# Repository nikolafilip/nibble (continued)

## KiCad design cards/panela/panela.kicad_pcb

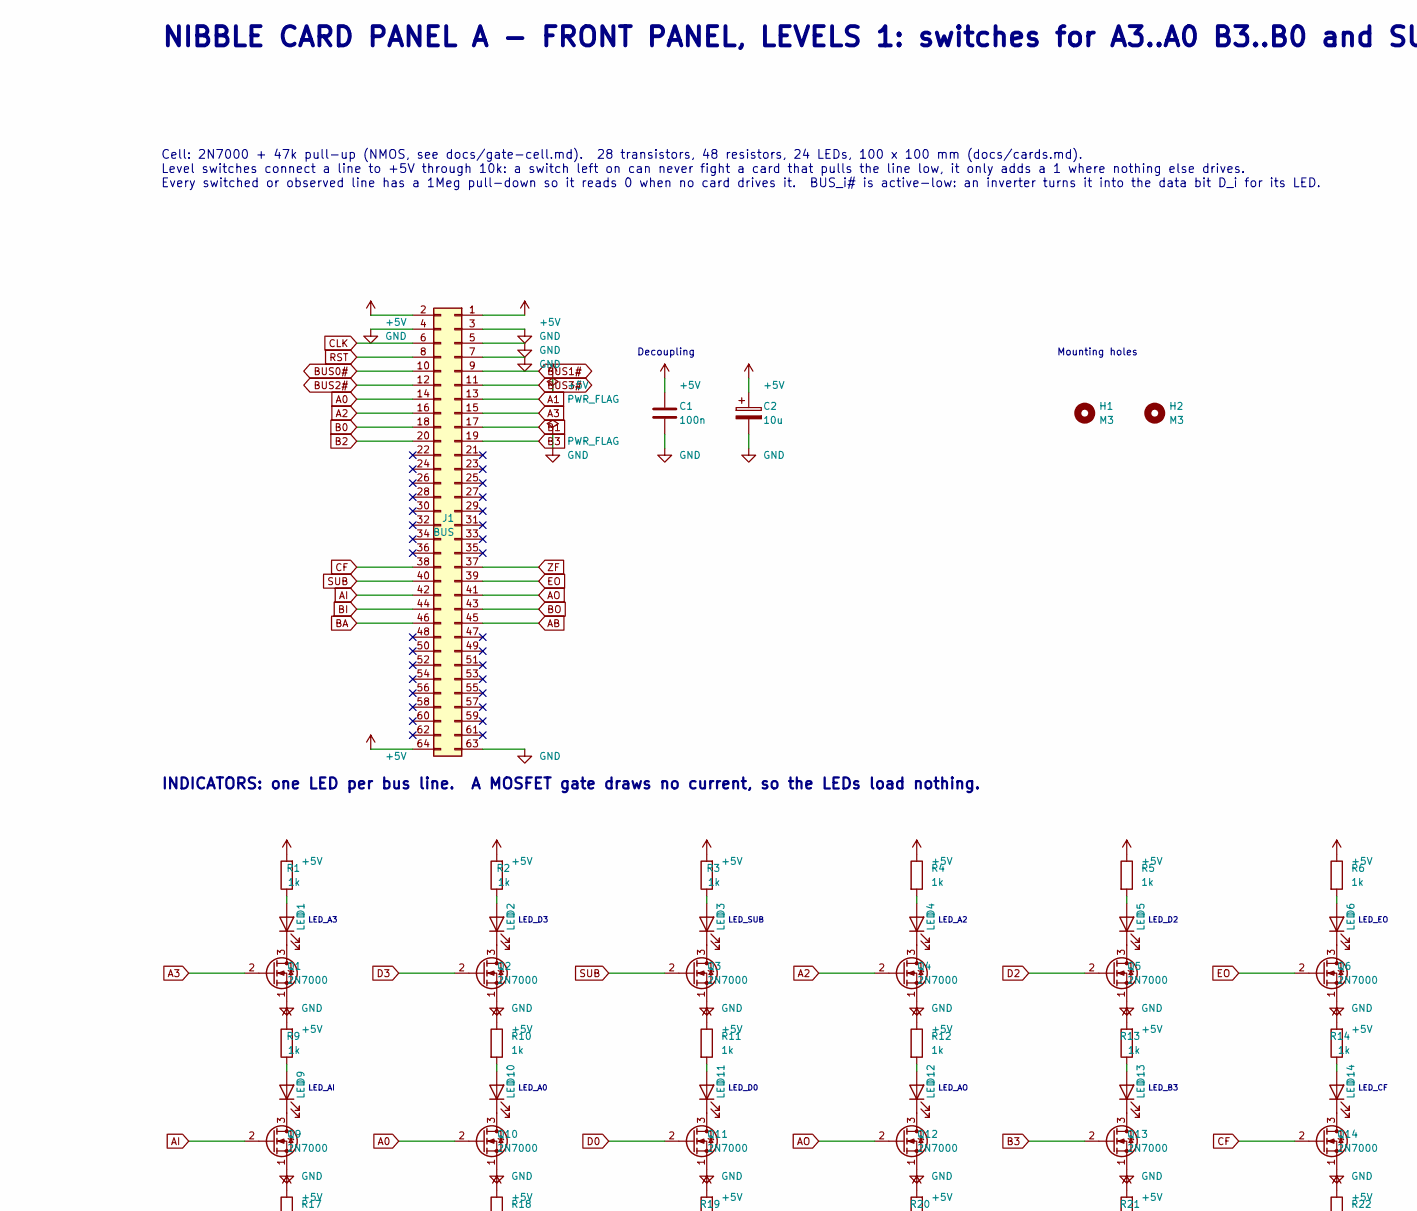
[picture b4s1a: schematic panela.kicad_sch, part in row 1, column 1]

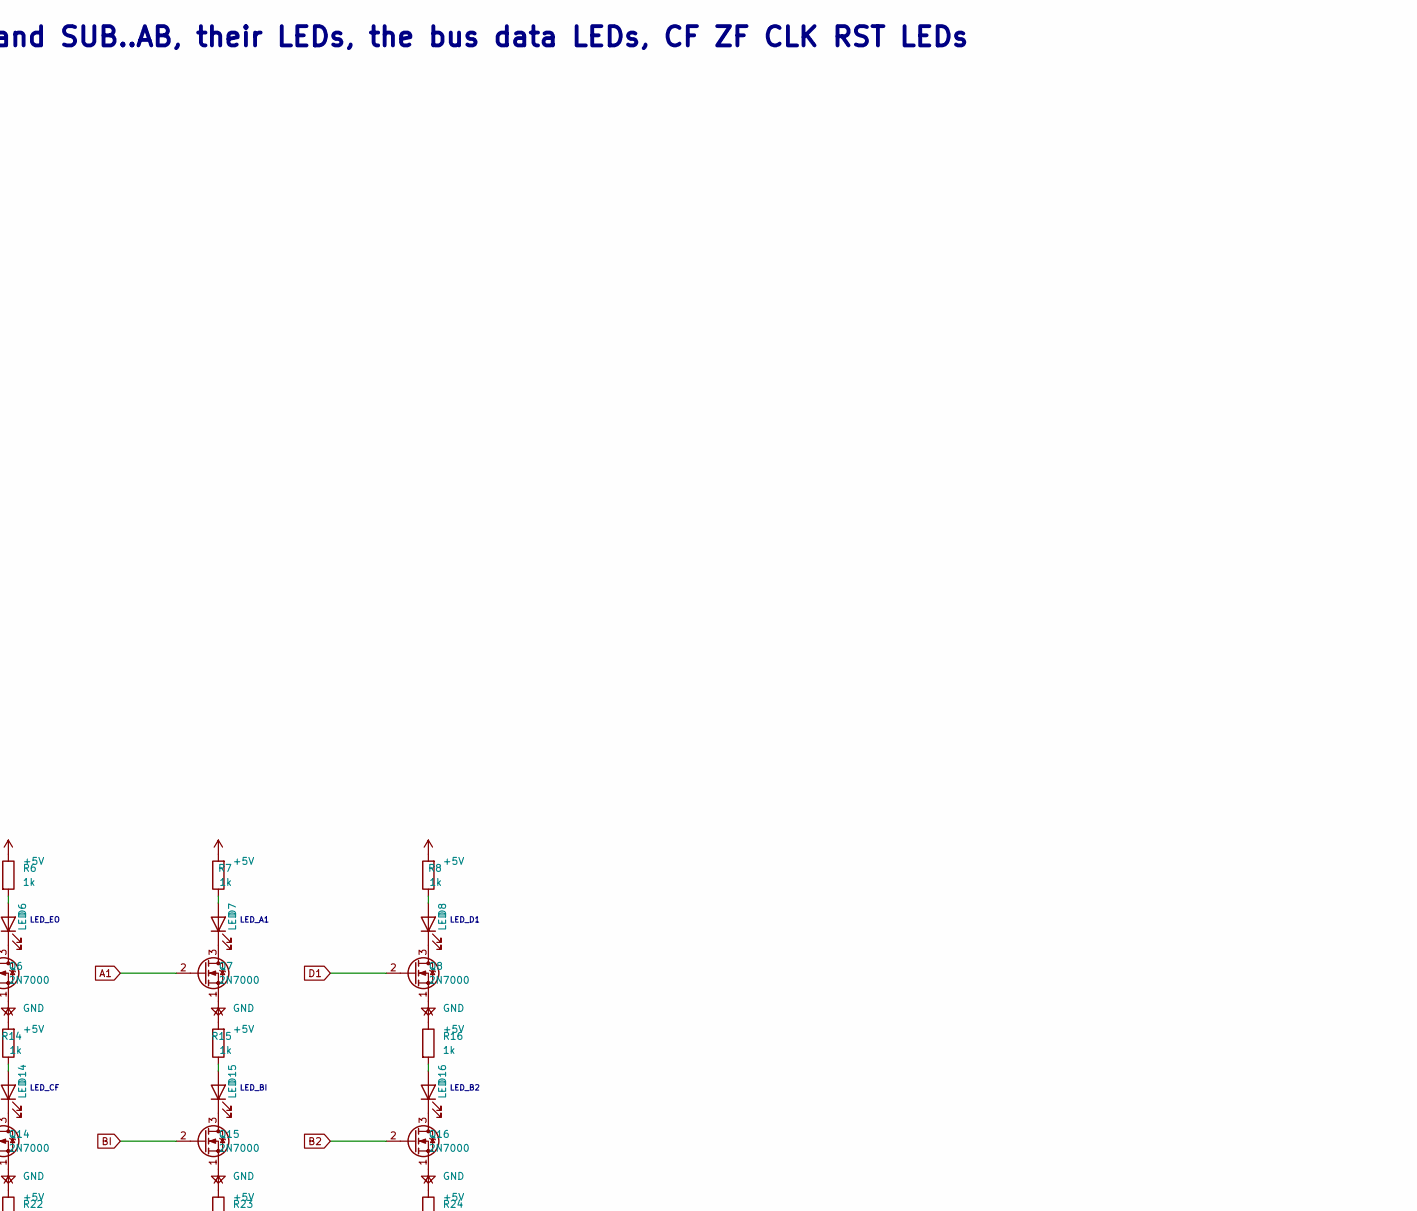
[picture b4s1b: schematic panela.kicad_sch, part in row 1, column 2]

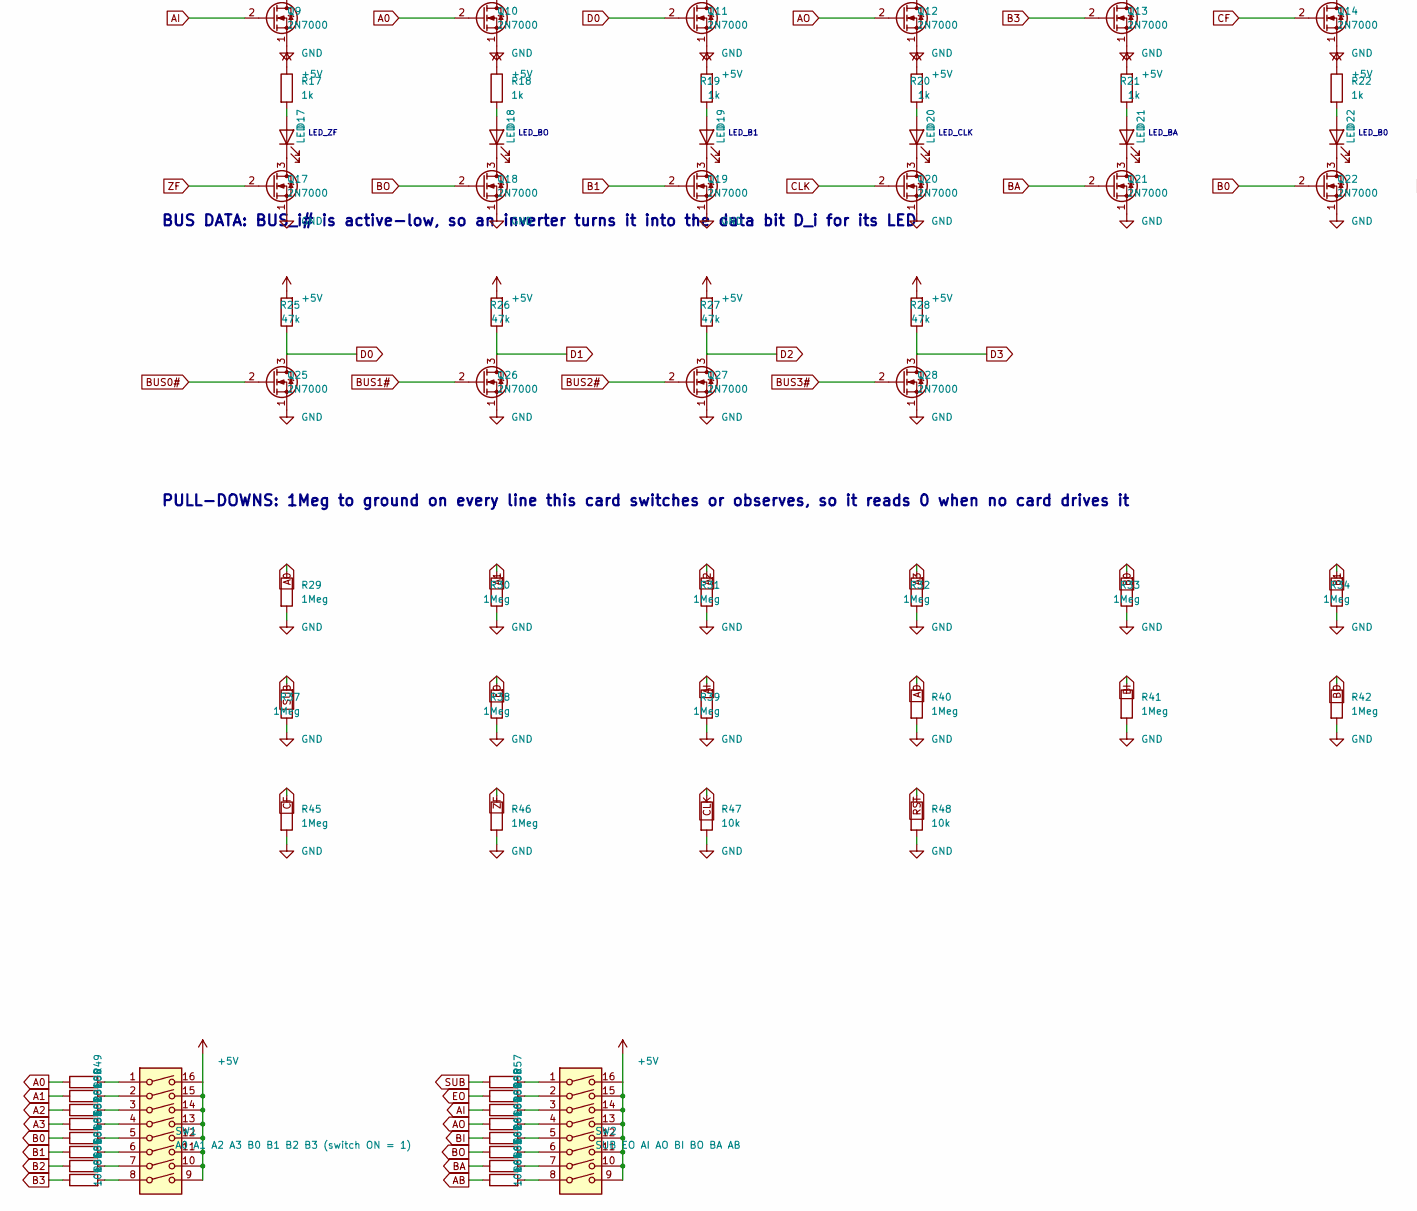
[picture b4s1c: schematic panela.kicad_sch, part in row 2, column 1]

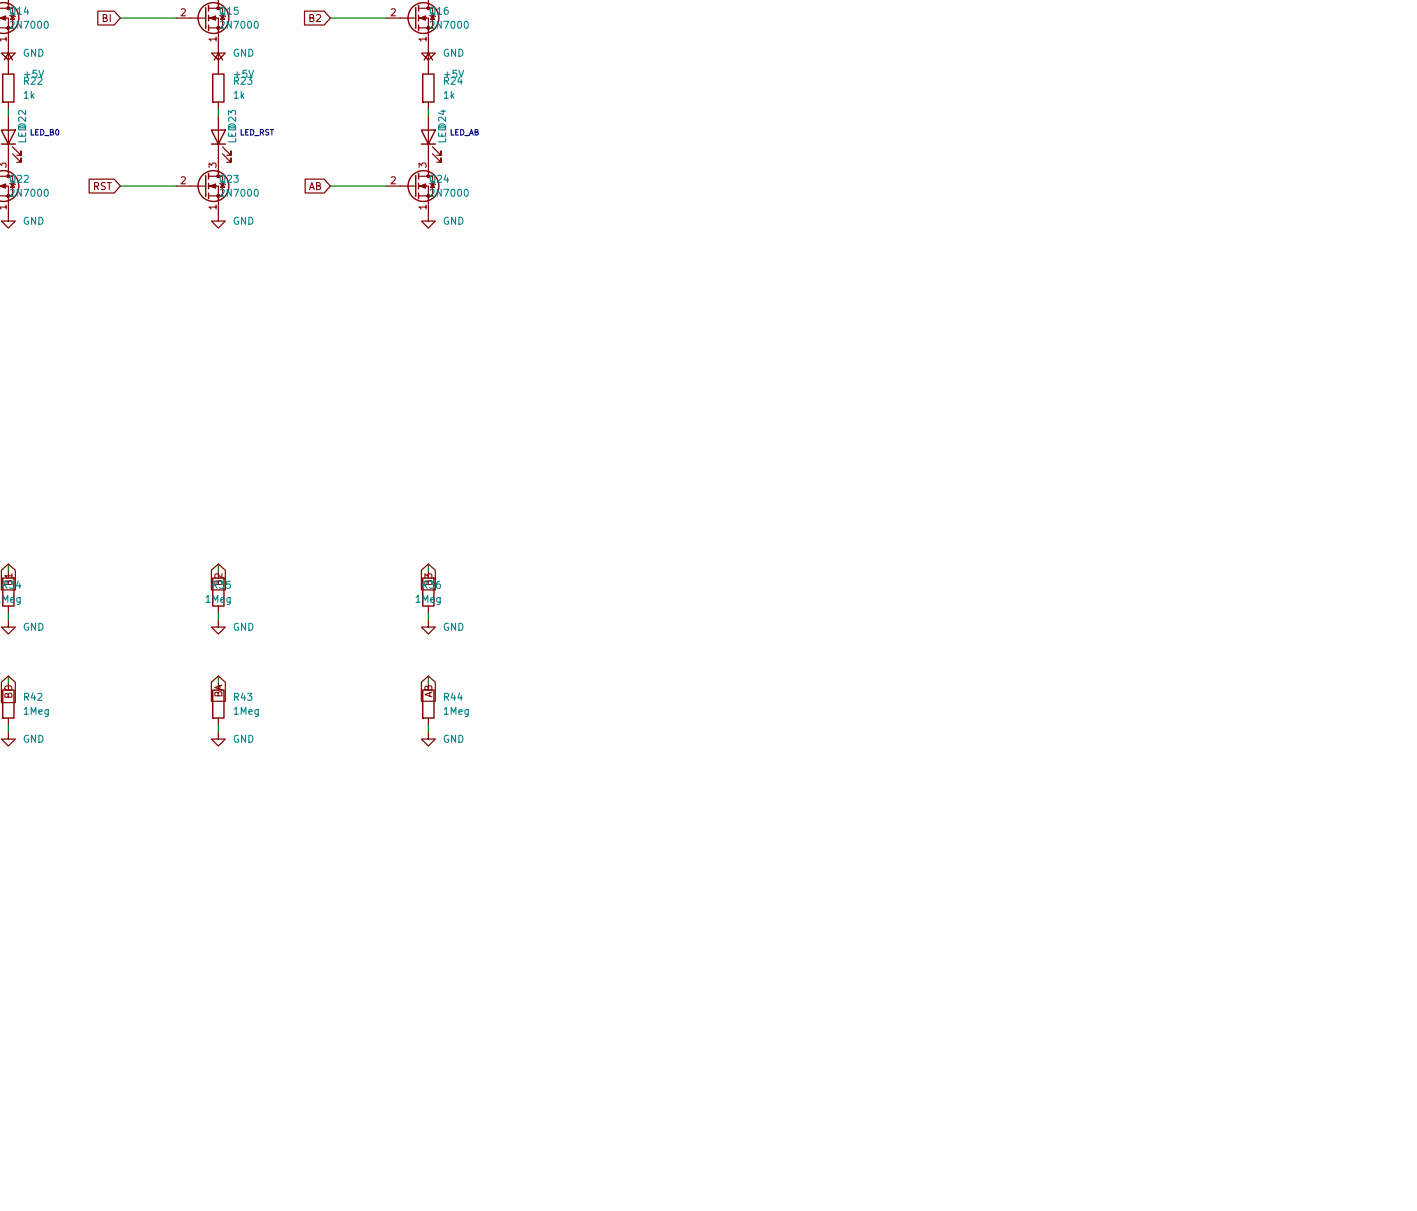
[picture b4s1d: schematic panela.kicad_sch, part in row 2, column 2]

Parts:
C1: 100n; C_Disc_D5.0mm_W2.5mm_P2.50mm
C2: 10u; CP_Radial_D5.0mm_P2.00mm
D1, D2, D3, D4, D5, D6, D7, D8, D9, D10, D11, D12, D13, D14, D15, D16, D17, D18, D19, D20, D21, D22, D23, D24: LED; LED_D3.0mm
H1, H2: M3; MountingHole_3.2mm_M3_Pad
J1: BUS; IDC-Header_2x32_P2.54mm_Vertical
Q1, Q2, Q3, Q4, Q5, Q6, Q7, Q8, Q9, Q10, Q11, Q12, Q13, Q14, Q15, Q16, Q17, Q18, Q19, Q20, Q21, Q22, Q23, Q24, Q25, Q26, Q27, Q28: 2N7000; TO-92_Inline_Wide
R1, R2, R3, R4, R5, R6, R7, R8, R9, R10, R11, R12, R13, R14, R15, R16, R17, R18, R19, R20, R21, R22, R23, R24: 1k; R_Axial_DIN0207_L6.3mm_D2.5mm_P5.08mm_Vertical
R25, R26, R27, R28: 47k; R_Axial_DIN0207_L6.3mm_D2.5mm_P5.08mm_Vertical
R29, R30, R31, R32, R33, R34, R35, R36, R37, R38, R39, R40, R41, R42, R43, R44, R45, R46: 1Meg; R_Axial_DIN0207_L6.3mm_D2.5mm_P5.08mm_Vertical
R47, R48, R49, R50, R51, R52, R53, R54, R55, R56, R57, R58, R59, R60, R61, R62, R63, R64: 10k; R_Axial_DIN0207_L6.3mm_D2.5mm_P5.08mm_Vertical
SW1: A0 A1 A2 A3 B0 B1 B2 B3 (switch ON = 1); SW_DIP_SPSTx08_Slide_9.78x22.5mm_W7.62mm_P2.54mm
SW2: SUB EO AI AO BI BO BA AB; SW_DIP_SPSTx08_Slide_9.78x22.5mm_W7.62mm_P2.54mm

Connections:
+5V: C1.1, C2.1, J1.1, J1.2, J1.64, R1.2, R2.2, R3.2, R4.1, R5.1, R6.1, R7.2, R8.2, R9.2, R10.1, R11.1, R12.1, R13.2, R14.2, R15.2, R16.1, R17.1, R18.1, R19.2, R20.2, R21.2, R22.1, R23.1, R24.1, R25.2, R26.2, R27.2, R28.2, SW1.9, SW1.10, SW1.11, SW1.12, SW1.13, SW1.14, SW1.15, SW1.16, SW2.9, SW2.10, SW2.11, SW2.12, SW2.13, SW2.14, SW2.15, SW2.16
A0: J1.14, Q10.2 (G), R29.1, R49.1
A1: J1.13, Q7.2 (G), R30.2, R50.1
A2: J1.16, Q4.2 (G), R31.2, R51.1
A3: J1.15, Q1.2 (G), R32.2, R52.1
AB: J1.45, Q24.2 (G), R44.1, R64.1
AI: J1.42, Q9.2 (G), R39.2, R59.1
AO: J1.41, Q12.2 (G), R40.1, R60.1
B0: J1.18, Q22.2 (G), R33.2, R53.1
B1: J1.17, Q19.2 (G), R34.2, R54.1
B2: J1.20, Q16.2 (G), R35.2, R55.1
B3: J1.19, Q13.2 (G), R36.2, R56.1
BA: J1.46, Q21.2 (G), R43.1, R63.1
BI: J1.44, Q15.2 (G), R41.1, R61.1
BO: J1.43, Q18.2 (G), R42.1, R62.1
BUS0#: J1.10, Q25.2 (G)
BUS1#: J1.9, Q26.2 (G)
BUS2#: J1.12, Q27.2 (G)
BUS3#: J1.11, Q28.2 (G)
CF: J1.38, Q14.2 (G), R45.1
CLK: J1.6, Q20.2 (G), R47.1
D0: Q11.2 (G), Q25.3 (D), R25.1
D1: Q8.2 (G), Q26.3 (D), R26.1
D2: Q5.2 (G), Q27.3 (D), R27.1
D3: Q2.2 (G), Q28.3 (D), R28.1
EO: J1.39, Q6.2 (G), R38.2, R58.1
GND: C1.2, C2.2, J1.3, J1.4, J1.5, J1.7, J1.63, Q1.1 (S), Q2.1 (S), Q3.1 (S), Q4.1 (S), Q5.1 (S), Q6.1 (S), Q7.1 (S), Q8.1 (S), Q9.1 (S), Q10.1 (S), Q11.1 (S), Q12.1 (S), Q13.1 (S), Q14.1 (S), Q15.1 (S), Q16.1 (S), Q17.1 (S), Q18.1 (S), Q19.1 (S), Q20.1 (S), Q21.1 (S), Q22.1 (S), Q23.1 (S), Q24.1 (S), Q25.1 (S), Q26.1 (S), Q27.1 (S), Q28.1 (S), R29.2, R30.1, R31.1, R32.1, R33.1, R34.1, R35.1, R36.1, R37.1, R38.1, R39.1, R40.2, R41.2, R42.2, R43.2, R44.2, R45.2, R46.2, R47.2, R48.2
unnamed: D1.2 (A), R1.1
unnamed: D1.1 (K), Q1.3 (D)
unnamed: D2.2 (A), R2.1
unnamed: D2.1 (K), Q2.3 (D)
unnamed: D3.2 (A), R3.1
unnamed: D3.1 (K), Q3.3 (D)
unnamed: D4.2 (A), R4.2
unnamed: D4.1 (K), Q4.3 (D)
unnamed: D5.2 (A), R5.2
unnamed: D5.1 (K), Q5.3 (D)
unnamed: D6.2 (A), R6.2
unnamed: D6.1 (K), Q6.3 (D)
unnamed: D7.2 (A), R7.1
unnamed: D7.1 (K), Q7.3 (D)
unnamed: D8.2 (A), R8.1
unnamed: D8.1 (K), Q8.3 (D)
unnamed: D9.2 (A), R9.1
unnamed: D9.1 (K), Q9.3 (D)
unnamed: D10.2 (A), R10.2
unnamed: D10.1 (K), Q10.3 (D)
unnamed: D11.2 (A), R11.2
unnamed: D11.1 (K), Q11.3 (D)
unnamed: D12.2 (A), R12.2
unnamed: D12.1 (K), Q12.3 (D)
unnamed: D13.2 (A), R13.1
unnamed: D13.1 (K), Q13.3 (D)
unnamed: D14.2 (A), R14.1
unnamed: D14.1 (K), Q14.3 (D)
unnamed: D15.2 (A), R15.1
unnamed: D15.1 (K), Q15.3 (D)
unnamed: D16.2 (A), R16.2
unnamed: D16.1 (K), Q16.3 (D)
unnamed: D17.2 (A), R17.2
unnamed: D17.1 (K), Q17.3 (D)
unnamed: D18.2 (A), R18.2
unnamed: D18.1 (K), Q18.3 (D)
unnamed: D19.2 (A), R19.1
unnamed: D19.1 (K), Q19.3 (D)
unnamed: D20.2 (A), R20.1
unnamed: D20.1 (K), Q20.3 (D)
unnamed: D21.2 (A), R21.1
unnamed: D21.1 (K), Q21.3 (D)
unnamed: D22.2 (A), R22.2
unnamed: D22.1 (K), Q22.3 (D)
unnamed: D23.2 (A), R23.2
unnamed: D23.1 (K), Q23.3 (D)
unnamed: D24.2 (A), R24.2
unnamed: D24.1 (K), Q24.3 (D)
unnamed: R49.2, SW1.1
unnamed: R50.2, SW1.2
unnamed: R51.2, SW1.3
unnamed: R52.2, SW1.4
unnamed: R53.2, SW1.5
unnamed: R54.2, SW1.6
unnamed: R55.2, SW1.7
unnamed: R56.2, SW1.8
unnamed: R57.2, SW2.1
unnamed: R58.2, SW2.2
unnamed: R59.2, SW2.3
unnamed: R60.2, SW2.4
unnamed: R61.2, SW2.5
unnamed: R62.2, SW2.6
unnamed: R63.2, SW2.7
unnamed: R64.2, SW2.8
RST: J1.8, Q23.2 (G), R48.1
SUB: J1.40, Q3.2 (G), R37.2, R57.1
ZF: J1.37, Q17.2 (G), R46.1

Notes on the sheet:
NIBBLE CARD PANEL A - FRONT PANEL, LEVELS 1: switches for A3..A0 B3..B0 and SUB..AB, their LEDs, the bus data LEDs, CF ZF CLK RST LEDs
Cell: 2N7000 + 47k pull-up (NMOS, see docs/gate-cell.md). 28 transistors, 48 resistors, 24 LEDs, 100 x 100 mm (docs/cards.md). Level switches connect a line to +5V through 10k: a switch left on can never fight a card that pulls the line low, it only adds a 1 where nothing else drives. Every switche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
INDICATORS: one LED per bus line. A MOSFET gate draws no current, so the LEDs load nothing.
LED_A3
LED_D3
LED_SUB
LED_A2
LED_D2
LED_EO
LED_A1
LED_D1
LED_AI
LED_A0
LED_D0
LED_AO
LED_B3
LED_CF
LED_BI
LED_B2
LED_ZF
LED_BO
LED_B1
LED_CLK
LED_BA
LED_B0
LED_RST
LED_AB
BUS DATA: BUS_i# is active-low, so an inverter turns it into the data bit D_i for its LED
PULL-DOWNS: 1Meg to ground on every line this card switches or observes, so it reads 0 when no card drives it
Decoupling
Mounting holes

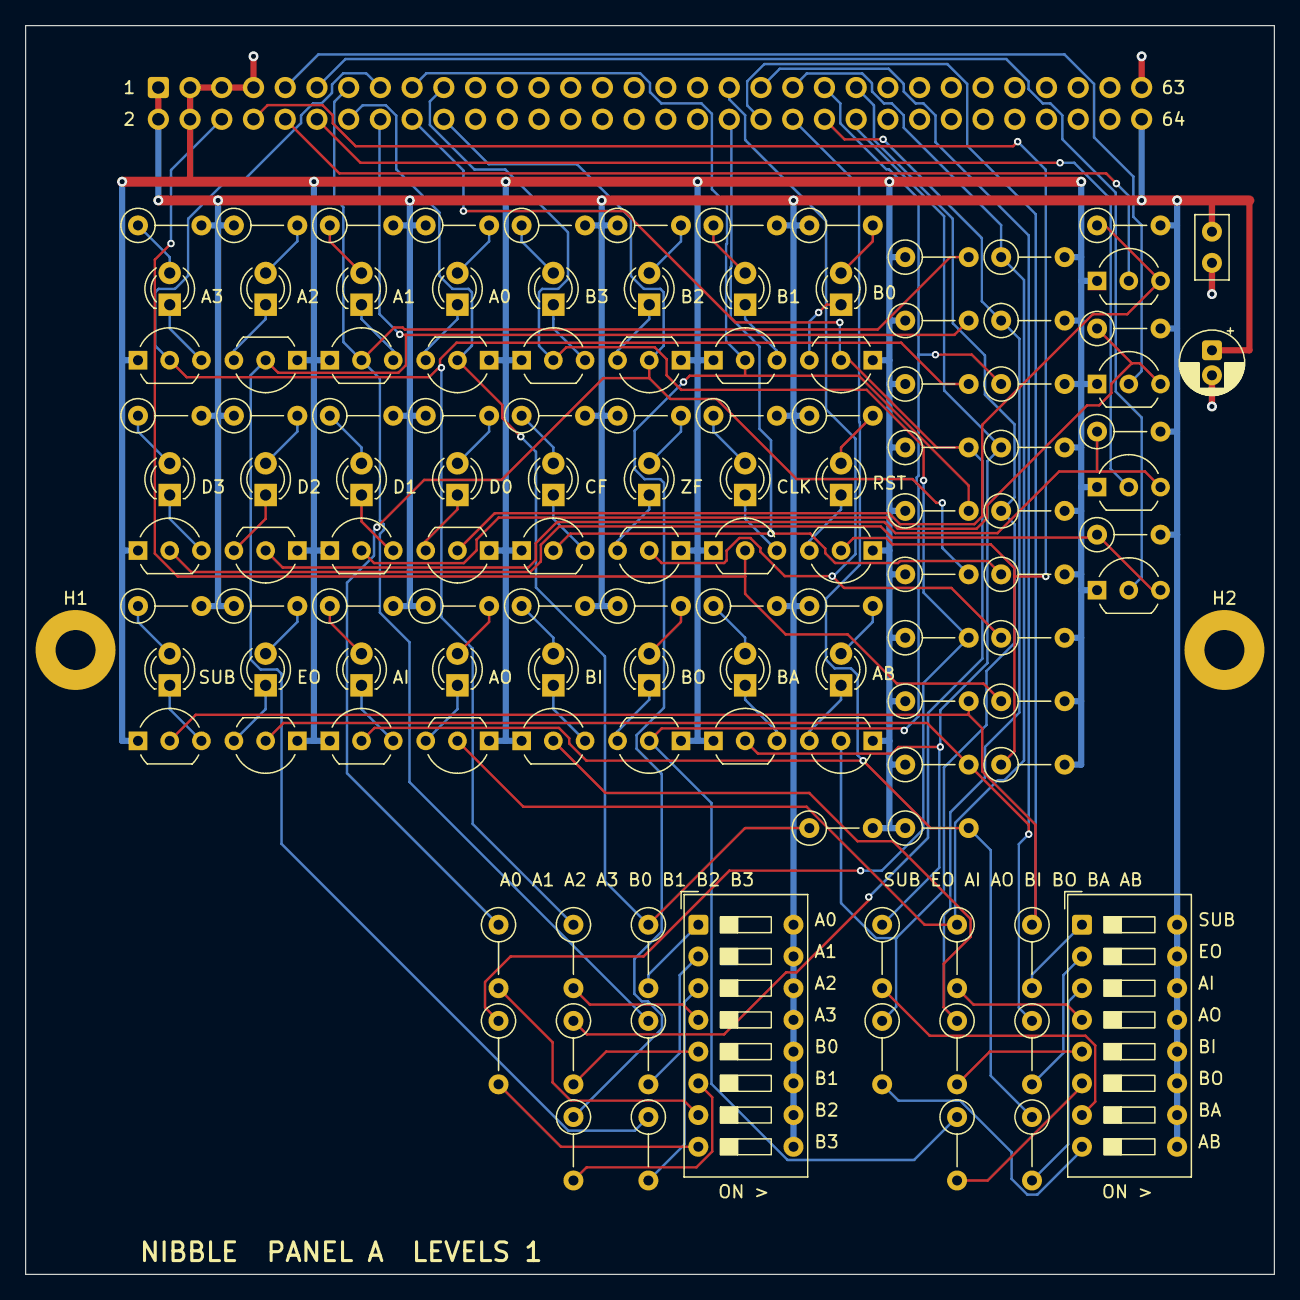
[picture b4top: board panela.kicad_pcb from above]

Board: 2 copper layers, 100.0 x 100.0 mm, 123 parts (1 on the bottom side), 94 nets.

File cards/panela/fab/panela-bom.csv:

"Reference","Value","Footprint","QUANTITY"
"C1","100n","Capacitor_THT:C_Disc_D5.0mm_W2.5mm_P2.50mm","1"
"C2","10u","Capacitor_THT:CP_Radial_D5.0mm_P2.00mm","1"
"D1-D24","LED","LED_THT:LED_D3.0mm","24"
"J1","BUS","Connector_IDC:IDC-Header_2x32_P2.54mm_Vertical","1"
"Q1-Q28","2N7000","Package_TO_SOT_THT:TO-92_Inline_Wide","28"
"R1-R24","1k","Resistor_THT:R_Axial_DIN0207_L6.3mm_D2.5mm_P5.08mm_Vertical","24"
"R25-R28","47k","Resistor_THT:R_Axial_DIN0207_L6.3mm_D2.5mm_P5.08mm_Vertical","4"
"R29-R46","1Meg","Resistor_THT:R_Axial_DIN0207_L6.3mm_D2.5mm_P5.08mm_Vertical","18"
"R47-R64","10k","Resistor_THT:R_Axial_DIN0207_L6.3mm_D2.5mm_P5.08mm_Vertical","18"
"SW1","A0 A1 A2 A3 B0 B1 B2 B3 (switch ON = 1)","Button_Switch_THT:SW_DIP_SPSTx08_Slide_9.78x22.5mm_W7.62mm_P2.54mm","1"
"SW2","SUB EO AI AO BI BO BA AB","Button_Switch_THT:SW_DIP_SPSTx08_Slide_9.78x22.5mm_W7.62mm_P2.54mm","1"

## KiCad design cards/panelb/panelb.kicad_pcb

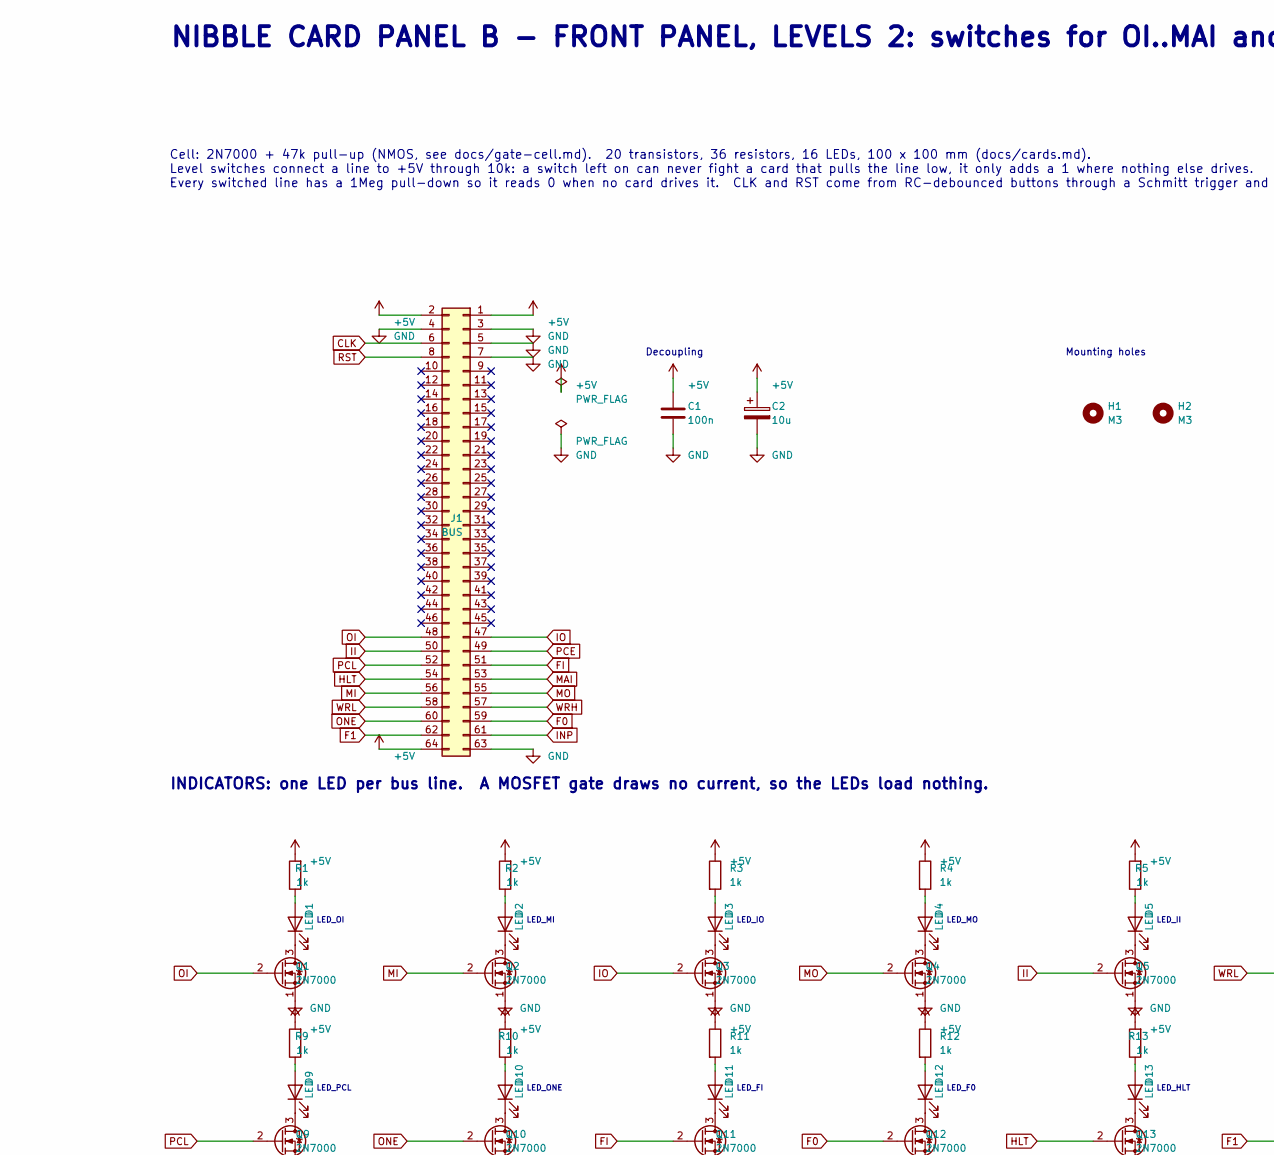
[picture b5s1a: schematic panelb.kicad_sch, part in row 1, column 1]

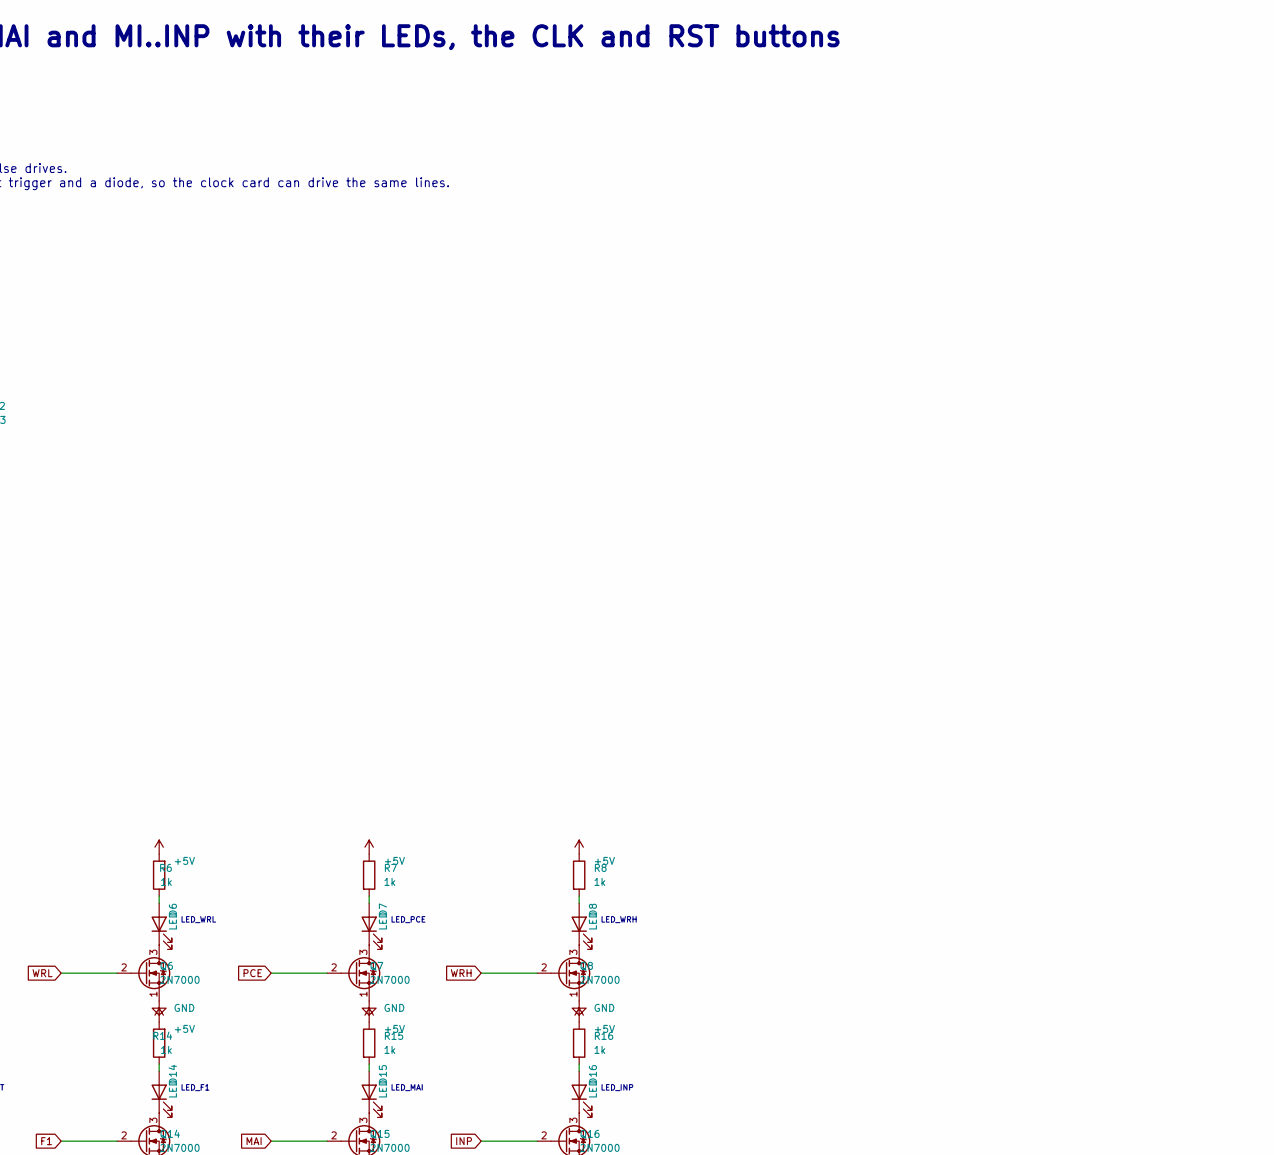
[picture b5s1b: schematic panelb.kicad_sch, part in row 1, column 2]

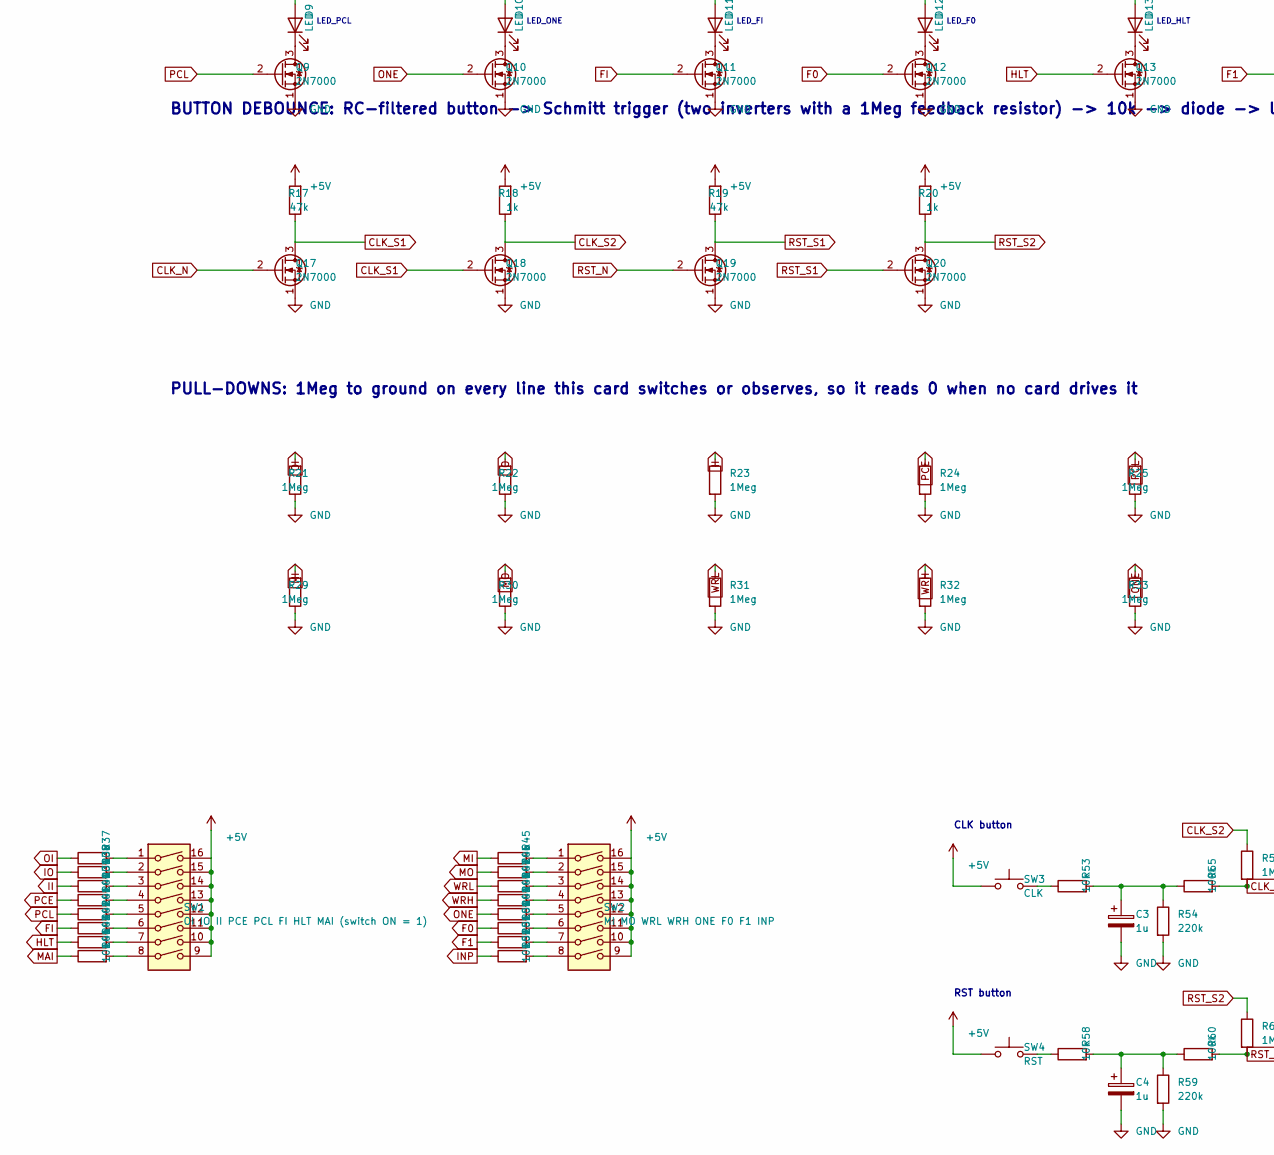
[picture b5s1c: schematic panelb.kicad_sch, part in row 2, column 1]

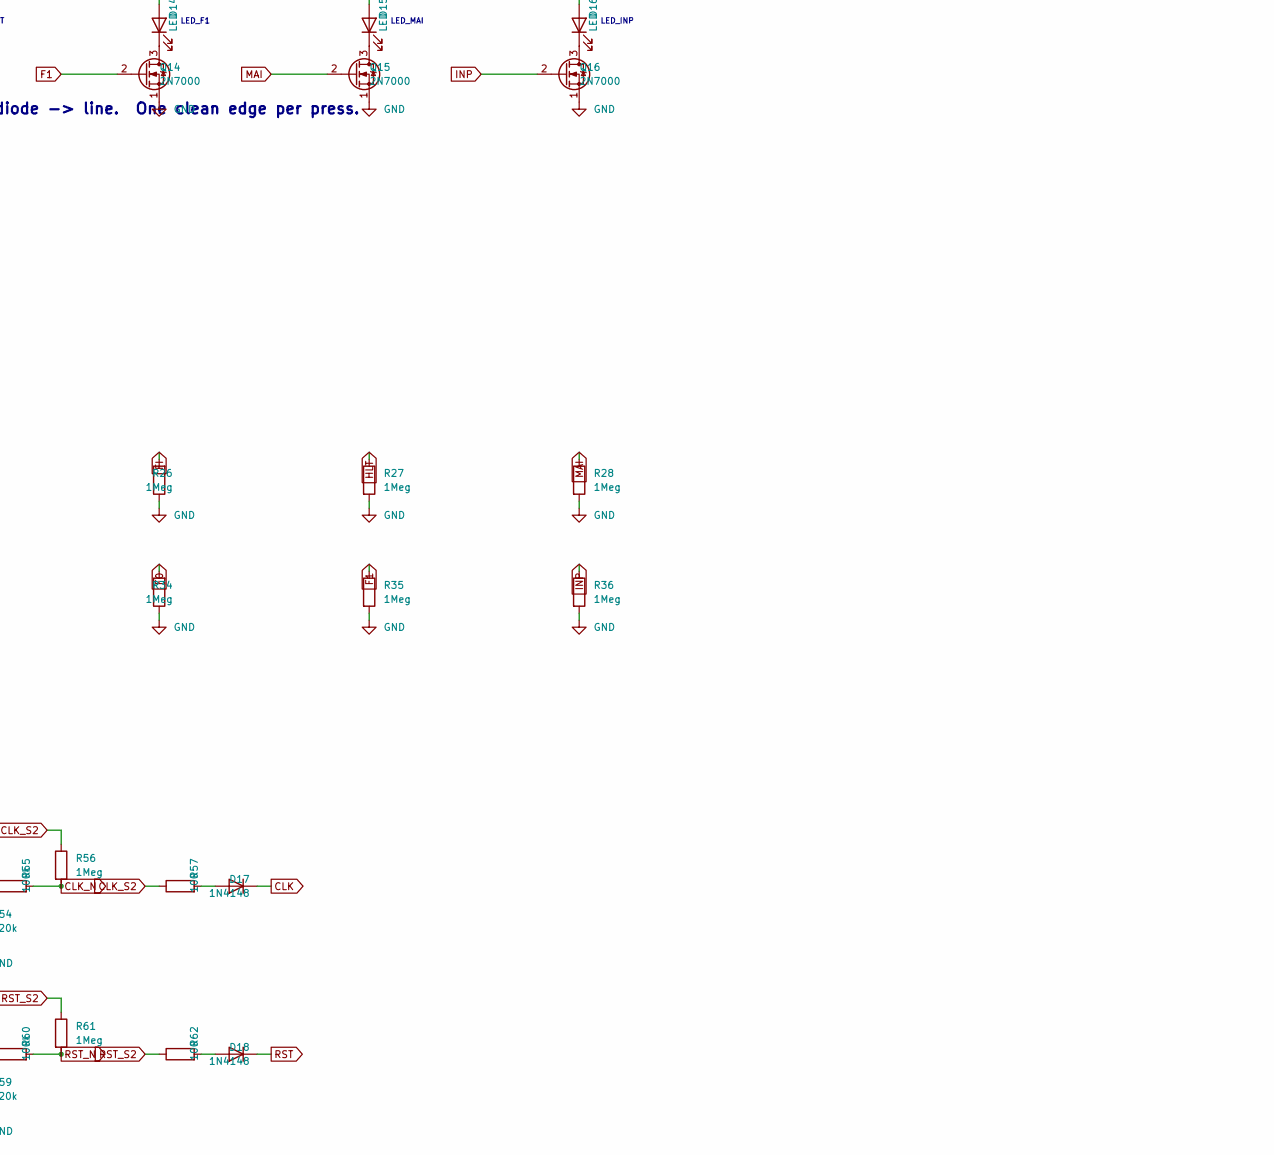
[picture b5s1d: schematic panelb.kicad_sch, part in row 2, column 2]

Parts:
C1: 100n; C_Disc_D5.0mm_W2.5mm_P2.50mm
C2: 10u; CP_Radial_D5.0mm_P2.00mm
C3, C4: 1u; CP_Radial_D5.0mm_P2.00mm
D1, D2, D3, D4, D5, D6, D7, D8, D9, D10, D11, D12, D13, D14, D15, D16: LED; LED_D3.0mm
D17, D18: 1N4148; D_DO-35_SOD27_P7.62mm_Horizontal
H1, H2: M3; MountingHole_3.2mm_M3_Pad
J1: BUS; IDC-Header_2x32_P2.54mm_Vertical
Q1, Q2, Q3, Q4, Q5, Q6, Q7, Q8, Q9, Q10, Q11, Q12, Q13, Q14, Q15, Q16, Q17, Q18, Q19, Q20: 2N7000; TO-92_Inline_Wide
R1, R2, R3, R4, R5, R6, R7, R8, R9, R10, R11, R12, R13, R14, R15, R16, R18, R20: 1k; R_Axial_DIN0207_L6.3mm_D2.5mm_P5.08mm_Vertical
R17, R19: 47k; R_Axial_DIN0207_L6.3mm_D2.5mm_P5.08mm_Vertical
R21, R22, R23, R24, R25, R26, R27, R28, R29, R30, R31, R32, R33, R34, R35, R36, R56, R61: 1Meg; R_Axial_DIN0207_L6.3mm_D2.5mm_P5.08mm_Vertical
R37, R38, R39, R40, R41, R42, R43, R44, R45, R46, R47, R48, R49, R50, R51, R52, R53, R58: 10k; R_Axial_DIN0207_L6.3mm_D2.5mm_P5.08mm_Vertical
R54, R59: 220k; R_Axial_DIN0207_L6.3mm_D2.5mm_P5.08mm_Vertical
R55, R60: 100k; R_Axial_DIN0207_L6.3mm_D2.5mm_P5.08mm_Vertical
R57, R62: 100; R_Axial_DIN0207_L6.3mm_D2.5mm_P5.08mm_Vertical
SW1: OI IO II PCE PCL FI HLT MAI (switch ON = 1); SW_DIP_SPSTx08_Slide_9.78x22.5mm_W7.62mm_P2.54mm
SW2: MI MO WRL WRH ONE F0 F1 INP; SW_DIP_SPSTx08_Slide_9.78x22.5mm_W7.62mm_P2.54mm
SW3: CLK; SW_PUSH_6mm
SW4: RST; SW_PUSH_6mm

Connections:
+5V: C1.1, C2.1, J1.1, J1.2, J1.64, R1.2, R2.2, R3.1, R4.1, R5.2, R6.2, R7.1, R8.1, R9.2, R10.2, R11.1, R12.1, R13.2, R14.2, R15.1, R16.1, R17.2, R18.2, R19.2, R20.2, SW1.9, SW1.10, SW1.11, SW1.12, SW1.13, SW1.14, SW1.15, SW1.16, SW2.9, SW2.10, SW2.11, SW2.12, SW2.13, SW2.14, SW2.15, SW2.16, SW3.1, SW4.1
CLK: D17.1 (K), J1.6
CLK_N: Q17.2 (G), R55.2, R56.2
CLK_S1: Q17.3 (D), Q18.2 (G), R17.1
CLK_S2: Q18.3 (D), R18.1, R56.1, R57.1
F0: J1.59, Q12.2 (G), R34.2, R50.1
F1: J1.62, Q14.2 (G), R35.1, R51.1
FI: J1.51, Q11.2 (G), R26.2, R42.1
GND: C1.2, C2.2, C3.2, C4.2, J1.3, J1.4, J1.5, J1.7, J1.63, Q1.1 (S), Q2.1 (S), Q3.1 (S), Q4.1 (S), Q5.1 (S), Q6.1 (S), Q7.1 (S), Q8.1 (S), Q9.1 (S), Q10.1 (S), Q11.1 (S), Q12.1 (S), Q13.1 (S), Q14.1 (S), Q15.1 (S), Q16.1 (S), Q17.1 (S), Q18.1 (S), Q19.1 (S), Q20.1 (S), R21.1, R22.1, R23.2, R24.2, R25.1, R26.1, R27.2, R28.2, R29.1, R30.1, R31.2, R32.2, R33.1, R34.1, R35.2, R36.2, R54.2, R59.2
HLT: J1.54, Q13.2 (G), R27.1, R43.1
II: J1.50, Q5.2 (G), R23.1, R39.1
INP: J1.61, Q16.2 (G), R36.1, R52.1
IO: J1.47, Q3.2 (G), R22.2, R38.1
MAI: J1.53, Q15.2 (G), R28.1, R44.1
MI: J1.56, Q2.2 (G), R29.2, R45.1
MO: J1.55, Q4.2 (G), R30.2, R46.1
unnamed: C3.1, R53.2, R54.1, R55.1
unnamed: C4.1, R58.2, R59.1, R60.1
unnamed: D1.2 (A), R1.1
unnamed: D1.1 (K), Q1.3 (D)
unnamed: D2.2 (A), R2.1
unnamed: D2.1 (K), Q2.3 (D)
unnamed: D3.2 (A), R3.2
unnamed: D3.1 (K), Q3.3 (D)
unnamed: D4.2 (A), R4.2
unnamed: D4.1 (K), Q4.3 (D)
unnamed: D5.2 (A), R5.1
unnamed: D5.1 (K), Q5.3 (D)
unnamed: D6.2 (A), R6.1
unnamed: D6.1 (K), Q6.3 (D)
unnamed: D7.2 (A), R7.2
unnamed: D7.1 (K), Q7.3 (D)
unnamed: D8.2 (A), R8.2
unnamed: D8.1 (K), Q8.3 (D)
unnamed: D9.2 (A), R9.1
unnamed: D9.1 (K), Q9.3 (D)
unnamed: D10.2 (A), R10.1
unnamed: D10.1 (K), Q10.3 (D)
unnamed: D11.2 (A), R11.2
unnamed: D11.1 (K), Q11.3 (D)
unnamed: D12.2 (A), R12.2
unnamed: D12.1 (K), Q12.3 (D)
unnamed: D13.2 (A), R13.1
unnamed: D13.1 (K), Q13.3 (D)
unnamed: D14.2 (A), R14.1
unnamed: D14.1 (K), Q14.3 (D)
unnamed: D15.2 (A), R15.2
unnamed: D15.1 (K), Q15.3 (D)
unnamed: D16.2 (A), R16.2
unnamed: D16.1 (K), Q16.3 (D)
unnamed: D17.2 (A), R57.2
unnamed: D18.2 (A), R62.2
unnamed: R37.2, SW1.1
unnamed: R38.2, SW1.2
unnamed: R39.2, SW1.3
unnamed: R40.2, SW1.4
unnamed: R41.2, SW1.5
unnamed: R42.2, SW1.6
unnamed: R43.2, SW1.7
unnamed: R44.2, SW1.8
unnamed: R45.2, SW2.1
unnamed: R46.2, SW2.2
unnamed: R47.2, SW2.3
unnamed: R48.2, SW2.4
unnamed: R49.2, SW2.5
unnamed: R50.2, SW2.6
unnamed: R51.2, SW2.7
unnamed: R52.2, SW2.8
unnamed: R53.1, SW3.2
unnamed: R58.1, SW4.2
OI: J1.48, Q1.2 (G), R21.2, R37.1
ONE: J1.60, Q10.2 (G), R33.2, R49.1
PCE: J1.49, Q7.2 (G), R24.1, R40.1
PCL: J1.52, Q9.2 (G), R25.2, R41.1
RST: D18.1 (K), J1.8
RST_N: Q19.2 (G), R60.2, R61.2
RST_S1: Q19.3 (D), Q20.2 (G), R19.1
RST_S2: Q20.3 (D), R20.1, R61.1, R62.1
WRH: J1.57, Q8.2 (G), R32.1, R48.1
WRL: J1.58, Q6.2 (G), R31.1, R47.1

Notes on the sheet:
NIBBLE CARD PANEL B - FRONT PANEL, LEVELS 2: switches for OI..MAI and MI..INP with their LEDs, the CLK and RST buttons
Cell: 2N7000 + 47k pull-up (NMOS, see docs/gate-cell.md). 20 transistors, 36 resistors, 16 LEDs, 100 x 100 mm (docs/cards.md). Level switches connect a line to +5V through 10k: a switch left on can never fight a card that pulls the line low, it only adds a 1 where nothing else drives. Every switche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
INDICATORS: one LED per bus line. A MOSFET gate draws no current, so the LEDs load nothing.
LED_OI
LED_MI
LED_IO
LED_MO
LED_II
LED_WRL
LED_PCE
LED_WRH
LED_PCL
LED_ONE
LED_FI
LED_F0
LED_HLT
LED_F1
LED_MAI
LED_INP
BUTTON DEBOUNCE: RC-filtered button -> Schmitt trigger (two inverters with a 1Meg feedback resistor) -> 10k -> diode -> line. One clean edge per press.
PULL-DOWNS: 1Meg to ground on every line this card switches or observes, so it reads 0 when no card drives it
Decoupling
Mounting holes
CLK button
RST button
